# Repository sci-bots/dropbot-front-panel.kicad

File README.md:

# DropBot v3 front panel

The front panel board provides the power (+3.3V, +12V) and communication (i2c) bus for the other boards in the [DropBot v3 system][dropbot] and routes the high-voltage outputs from the switching boards to the pogo-pin board.

For more information, please visit https://sci-bots.com

[][sci-bots]

This design is open-source hardware released under a [Creative Commons Attribution-ShareAlike licence][cc-by-sa].

[][cc-by-sa]

[dropbot]: https://github.com/sci-bots/dropbot-v3
[sci-bots]: https://sci-bots.com/
[cc-by-sa]: http://creativecommons.org/licenses/by-sa/3.0

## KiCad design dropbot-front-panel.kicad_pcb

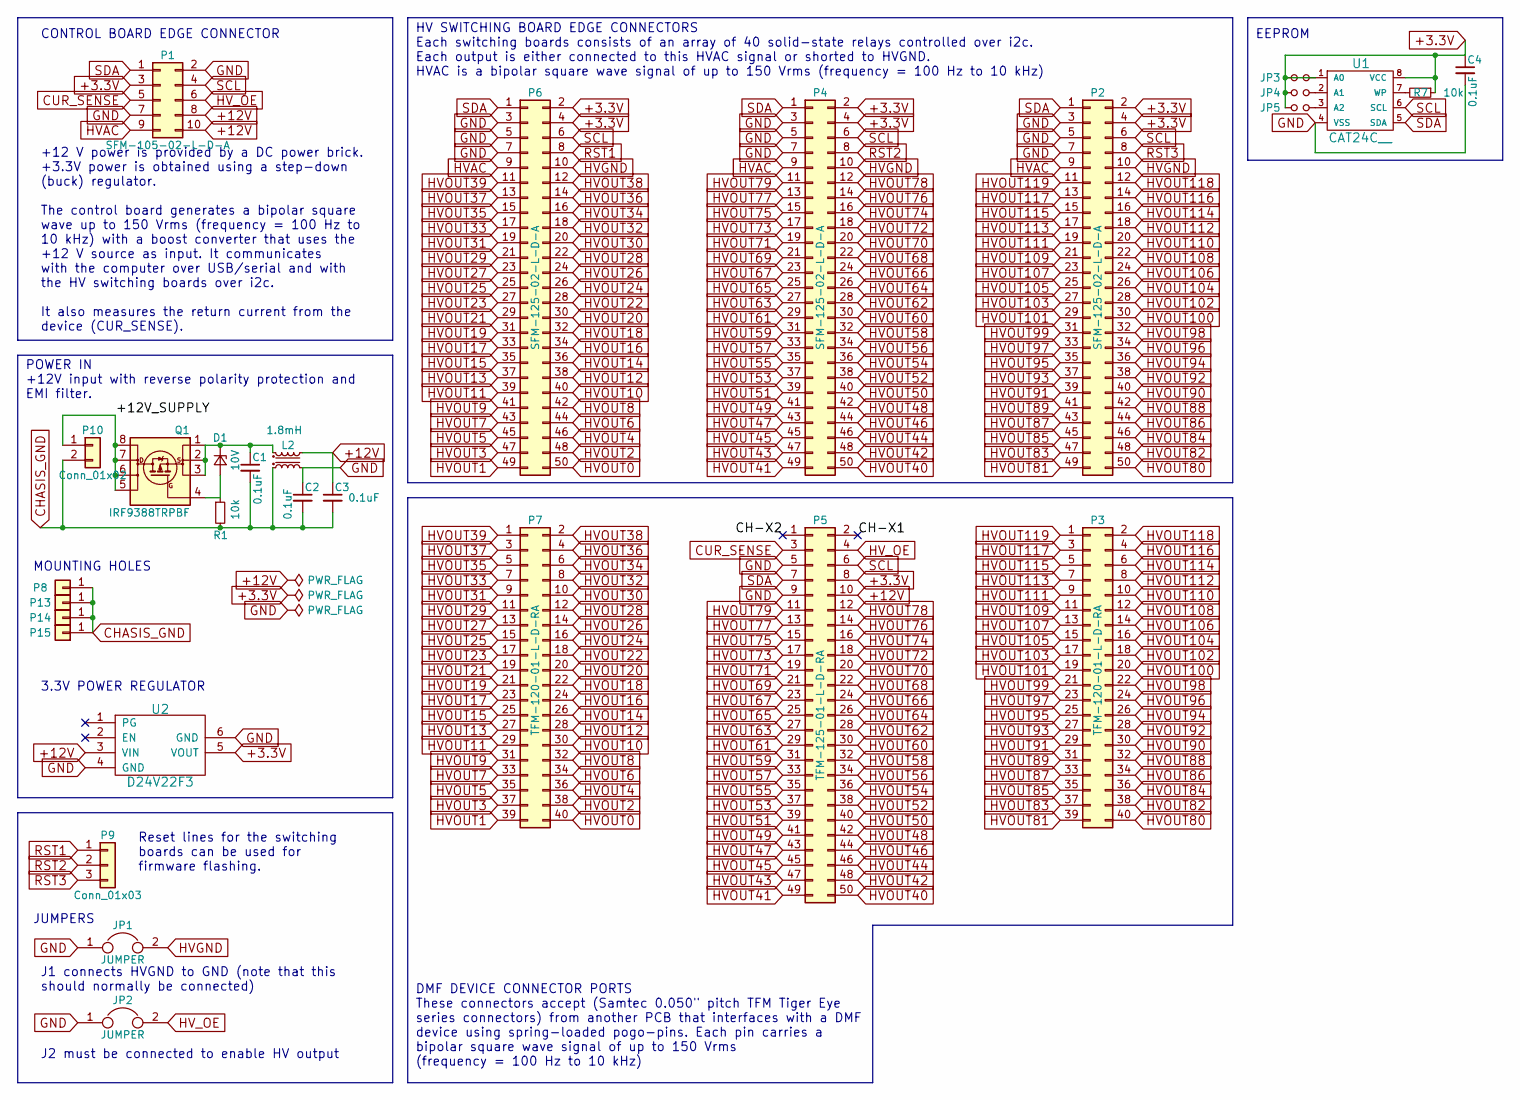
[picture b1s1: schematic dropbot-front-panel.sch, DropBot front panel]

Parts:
C1, C2, C3, C4: 0.1uF; C_0805; MPN CL21B104KBCNNNC
D1: 10V; D_SOD-323; MPN MMSZ5240BS-7-F
JP1: JUMPER; R_0805; MPN RC0805JR-070RL
JP2: JUMPER; R_0805; MPN DNP
JP3: A0; R_0603; MPN DNP
JP4: A1; R_0603; MPN DNP
JP5: A2; R_0603; MPN DNP
L2: 1.8mH; RN242-X-02-XXX; MPN RN242-6-02-1M8
P1: SFM-105-02-L-D-A; SFM-105-02-XXX-D-A; MPN SFM-105-02-L-D-A
P2, P4, P6: SFM-125-02-L-D-A; SFM-125-02-XXX-D-A; MPN TFM-120-01-L-D-RA
P3, P7: TFM-120-01-L-D-RA; TFM-120-01-XXX-D-RA; MPN TFM-125-01-L-D-RA
P5: TFM-125-01-L-D-RA; TFM-125-01-XXX-D-RA; MPN DNP
P8, P13, P14, P15: Conn_01x01; 1pin; MPN SFM-125-02-L-D-A
P9: Conn_01x03; Pin_Header_Straight_1x03; MPN DNP
P10: Conn_01x02; bornier2; MPN DNP
Q1: IRF9388TRPBF; SO-8; MPN IRF9388TRPBF
R1, R7: 10k; R_0805; MPN RC0805FR-0710KL
U1: CAT24C__; TSSOP-8_4.4x3mm_Pitch0.65mm; MPN M24C02-DRDW8TP/K
U2: D24V22F3; D24V22F; MPN D24V22F3

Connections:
+3.3V: C4.1, JP3.1, JP3.2, JP4.1, JP5.1, P1.3, P2.2, P2.4, P4.2, P4.4, P5.8, P6.2, P6.4, R7.1, U1.1 (A0), U1.8 (VCC), U2.5 (VOUT)
+12V: C3.1, L2.2, P1.8, P1.10, P5.10, U2.3 (VIN)
/+12V_SUPPLY: P10.1, Q1.5 (D), Q1.6 (D), Q1.7 (D), Q1.8 (D)
/CH-X1: P5.2
/CH-X2: P5.1
CHASIS_GND: C1.2, C2.2, C3.2, L2.4, P8.1, P10.2, P13.1, P14.1, P15.1, R1.2
CUR_SENSE: P1.5, P5.3
GND: C2.1, C4.2, JP1.1, JP2.1, L2.3, P1.2, P1.7, P2.3, P2.5, P2.7, P4.3, P4.5, P4.7, P5.5, P5.9, P6.3, P6.5, P6.7, U1.4 (VSS), U2.4 (GND), U2.6 (GND)
HVAC: P1.9, P2.9, P4.9, P6.9
HVGND: JP1.2, P2.10, P4.10, P6.10
HVOUT0: P6.50, P7.40
HVOUT1: P6.49, P7.39
HVOUT2: P6.48, P7.38
HVOUT3: P6.47, P7.37
HVOUT4: P6.46, P7.36
HVOUT5: P6.45, P7.35
HVOUT6: P6.44, P7.34
HVOUT7: P6.43, P7.33
HVOUT8: P6.42, P7.32
HVOUT9: P6.41, P7.31
HVOUT10: P6.40, P7.30
HVOUT11: P6.39, P7.29
HVOUT12: P6.38, P7.28
HVOUT13: P6.37, P7.27
HVOUT14: P6.36, P7.26
HVOUT15: P6.35, P7.25
HVOUT16: P6.34, P7.24
HVOUT17: P6.33, P7.23
HVOUT18: P6.32, P7.22
HVOUT19: P6.31, P7.21
HVOUT20: P6.30, P7.20
HVOUT21: P6.29, P7.19
HVOUT22: P6.28, P7.18
HVOUT23: P6.27, P7.17
HVOUT24: P6.26, P7.16
HVOUT25: P6.25, P7.15
HVOUT26: P6.24, P7.14
HVOUT27: P6.23, P7.13
HVOUT28: P6.22, P7.12
HVOUT29: P6.21, P7.11
HVOUT30: P6.20, P7.10
HVOUT31: P6.19, P7.9
HVOUT32: P6.18, P7.8
HVOUT33: P6.17, P7.7
HVOUT34: P6.16, P7.6
HVOUT35: P6.15, P7.5
HVOUT36: P6.14, P7.4
HVOUT37: P6.13, P7.3
HVOUT38: P6.12, P7.2
HVOUT39: P6.11, P7.1
HVOUT40: P4.50, P5.50
HVOUT41: P4.49, P5.49
HVOUT42: P4.48, P5.48
HVOUT43: P4.47, P5.47
HVOUT44: P4.46, P5.46
HVOUT45: P4.45, P5.45
HVOUT46: P4.44, P5.44
HVOUT47: P4.43, P5.43
HVOUT48: P4.42, P5.42
HVOUT49: P4.41, P5.41
HVOUT50: P4.40, P5.40
HVOUT51: P4.39, P5.39
HVOUT52: P4.38, P5.38
HVOUT53: P4.37, P5.37
HVOUT54: P4.36, P5.36
HVOUT55: P4.35, P5.35
HVOUT56: P4.34, P5.34
HVOUT57: P4.33, P5.33
HVOUT58: P4.32, P5.32
HVOUT59: P4.31, P5.31
HVOUT60: P4.30, P5.30
HVOUT61: P4.29, P5.29
HVOUT62: P4.28, P5.28
HVOUT63: P4.27, P5.27
HVOUT64: P4.26, P5.26
HVOUT65: P4.25, P5.25
HVOUT66: P4.24, P5.24
HVOUT67: P4.23, P5.23
HVOUT68: P4.22, P5.22
HVOUT69: P4.21, P5.21
HVOUT70: P4.20, P5.20
HVOUT71: P4.19, P5.19
HVOUT72: P4.18, P5.18
HVOUT73: P4.17, P5.17
HVOUT74: P4.16, P5.16
HVOUT75: P4.15, P5.15
HVOUT76: P4.14, P5.14
HVOUT77: P4.13, P5.13
HVOUT78: P4.12, P5.12
HVOUT79: P4.11, P5.11
HVOUT80: P2.50, P3.40
HVOUT81: P2.49, P3.39
HVOUT82: P2.48, P3.38
HVOUT83: P2.47, P3.37
HVOUT84: P2.46, P3.36
HVOUT85: P2.45, P3.35
HVOUT86: P2.44, P3.34
HVOUT87: P2.43, P3.33
HVOUT88: P2.42, P3.32
HVOUT89: P2.41, P3.31
HVOUT90: P2.40, P3.30
HVOUT91: P2.39, P3.29
HVOUT92: P2.38, P3.28
HVOUT93: P2.37, P3.27
HVOUT94: P2.36, P3.26
HVOUT95: P2.35, P3.25
HVOUT96: P2.34, P3.24
HVOUT97: P2.33, P3.23
HVOUT98: P2.32, P3.22
HVOUT99: P2.31, P3.21
HVOUT100: P2.30, P3.20
HVOUT101: P2.29, P3.19
HVOUT102: P2.28, P3.18
HVOUT103: P2.27, P3.17
HVOUT104: P2.26, P3.16
HVOUT105: P2.25, P3.15
HVOUT106: P2.24, P3.14
HVOUT107: P2.23, P3.13
HVOUT108: P2.22, P3.12
HVOUT109: P2.21, P3.11
HVOUT110: P2.20, P3.10
HVOUT111: P2.19, P3.9
HVOUT112: P2.18, P3.8
HVOUT113: P2.17, P3.7
HVOUT114: P2.16, P3.6
HVOUT115: P2.15, P3.5
HVOUT116: P2.14, P3.4
HVOUT117: P2.13, P3.3
HVOUT118: P2.12, P3.2
HVOUT119: P2.11, P3.1
HV_OE: JP2.2, P1.6, P5.4
unnamed: C1.1, D1.1 (K), L2.1, Q1.1 (S), Q1.2 (S), Q1.3 (S)
unnamed: D1.2 (A), Q1.4 (G), R1.1
unnamed: JP4.2, U1.2 (A1)
unnamed: JP5.2, U1.3 (A2)
unnamed: R7.2, U1.7 (WP)
RST1: P6.8, P9.1
RST2: P4.8, P9.2
RST3: P2.8, P9.3
SCL: P1.4, P2.6, P4.6, P5.6, P6.6, U1.6 (SCL)
SDA: P1.1, P2.1, P4.1, P5.7, P6.1, U1.5 (SDA)

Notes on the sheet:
CONTROL BOARD EDGE CONNECTOR
HV SWITCHING BOARD EDGE CONNECTORS Each switching boards consists of an array of 40 solid-state relays controlled over i2c. Each output is either connected to this HVAC signal or shorted to HVGND. HVAC is a bipolar square wave signal of up to 150 Vrms (frequency = 100 Hz to 10 kHz)
DMF DEVICE CONNECTOR PORTS These connectors accept (Samtec 0.050" pitch TFM Tiger Eye series connectors) from another PCB that interfaces with a DMF device using spring-loaded pogo-pins. Each pin carries a bipolar square wave signal of up to 150 Vrms (frequency = 100 Hz to 10 kHz)
JUMPERS
J1 connects HVGND to GND (note that this should normally be connected)
J2 must be connected to enable HV output
+12 V power is provided by a DC power brick. +3.3V power is obtained using a step-down (buck) regulator. The control board generates a bipolar square wave up to 150 Vrms (frequency = 100 Hz to 10 kHz) with a boost converter that uses the +12 V source as input. It communicates with the computer over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
Reset lines for the switching boards can be used for firmware flashing.
3.3V POWER REGULATOR
POWER IN +12V input with reverse polarity protection and EMI filter.
MOUNTING HOLES
EEPROM

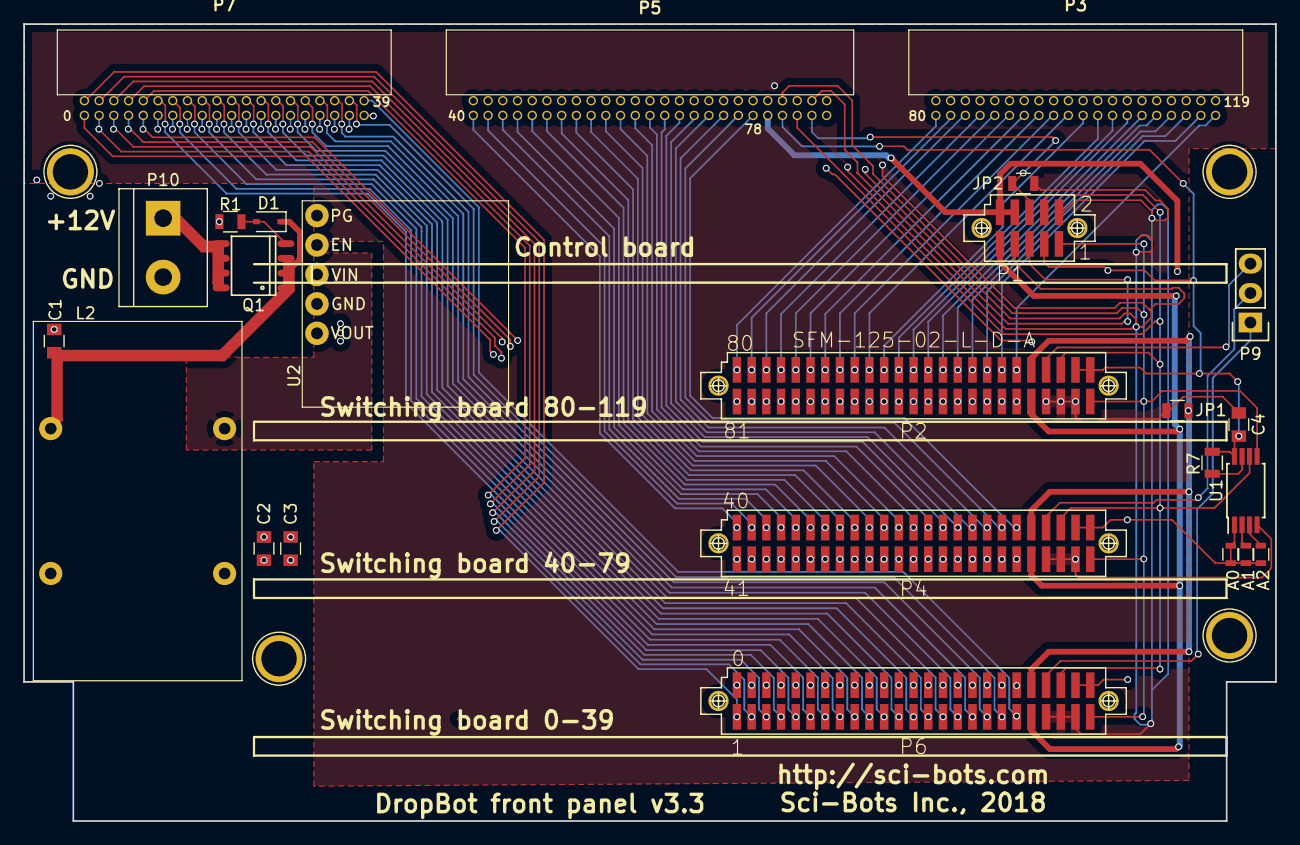
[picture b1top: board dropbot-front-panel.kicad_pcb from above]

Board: 4 copper layers, 108.0 x 68.8 mm, 29 parts (0 on the bottom side), 139 nets.

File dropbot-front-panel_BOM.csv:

Reference,Value,Footprint,Count,Datasheet,Mfg_Part_No
"JP1, JP2",JUMPER,Resistors_SMD:R_0805,2,,RC0805JR-070RL
U2,D24V22F3,Sci-Bots:D24V22F,1,,
Q1,IRF9388TRPBF,Power_Integrations:SO-8,1,,IRF9388TRPBF
L2,1.8mH,Sci-Bots:RN242-X-02-XXX,1,,RN242-6-02-1M8
"C1, C2, C3, C4",0.1uF,Capacitors_SMD:C_0805,4,,CL21B104KBCNNNC
"R1, R7",10k,Resistors_SMD:R_0805,2,,RC0805FR-0710KL
D1,10V,Diodes_SMD:D_SOD-323,1,,MMSZ5240BS-7-F
U1,I2C_EEPROM,Housings_SSOP:TSSOP-8_4.4x3mm_Pitch0.65mm,1,,M24C02-DRDW8TP/K
JP3,A0,Resistors_SMD:R_0603,1,,
JP4,A1,Resistors_SMD:R_0603,1,,
JP5,A2,Resistors_SMD:R_0603,1,,
P10,Conn_01x02,Connect:bornier2,1,,
"P8, P13, P14, P15",Conn_01x01,Connect:1pin,4,,
P9,Conn_01x03,Pin_Headers:Pin_Header_Straight_1x03,1,,
P1,SFM-105-02-L-D-A,Sci-Bots:SFM-105-02-XXX-D-A,1,,SFM-105-02-L-D-A
"P6, P4, P2",SFM-125-02-L-D-A,Sci-Bots:SFM-125-02-XXX-D-A,3,,SFM-125-02-L-D-A
"P7, P3",TFM-120-01-L-D-RA,Sci-Bots:TFM-120-01-XXX-D-RA,2,,TFM-120-01-L-D-RA
P5,TFM-125-01-L-D-RA,Sci-Bots:TFM-125-01-XXX-D-RA,1,,TFM-125-01-L-D-RA

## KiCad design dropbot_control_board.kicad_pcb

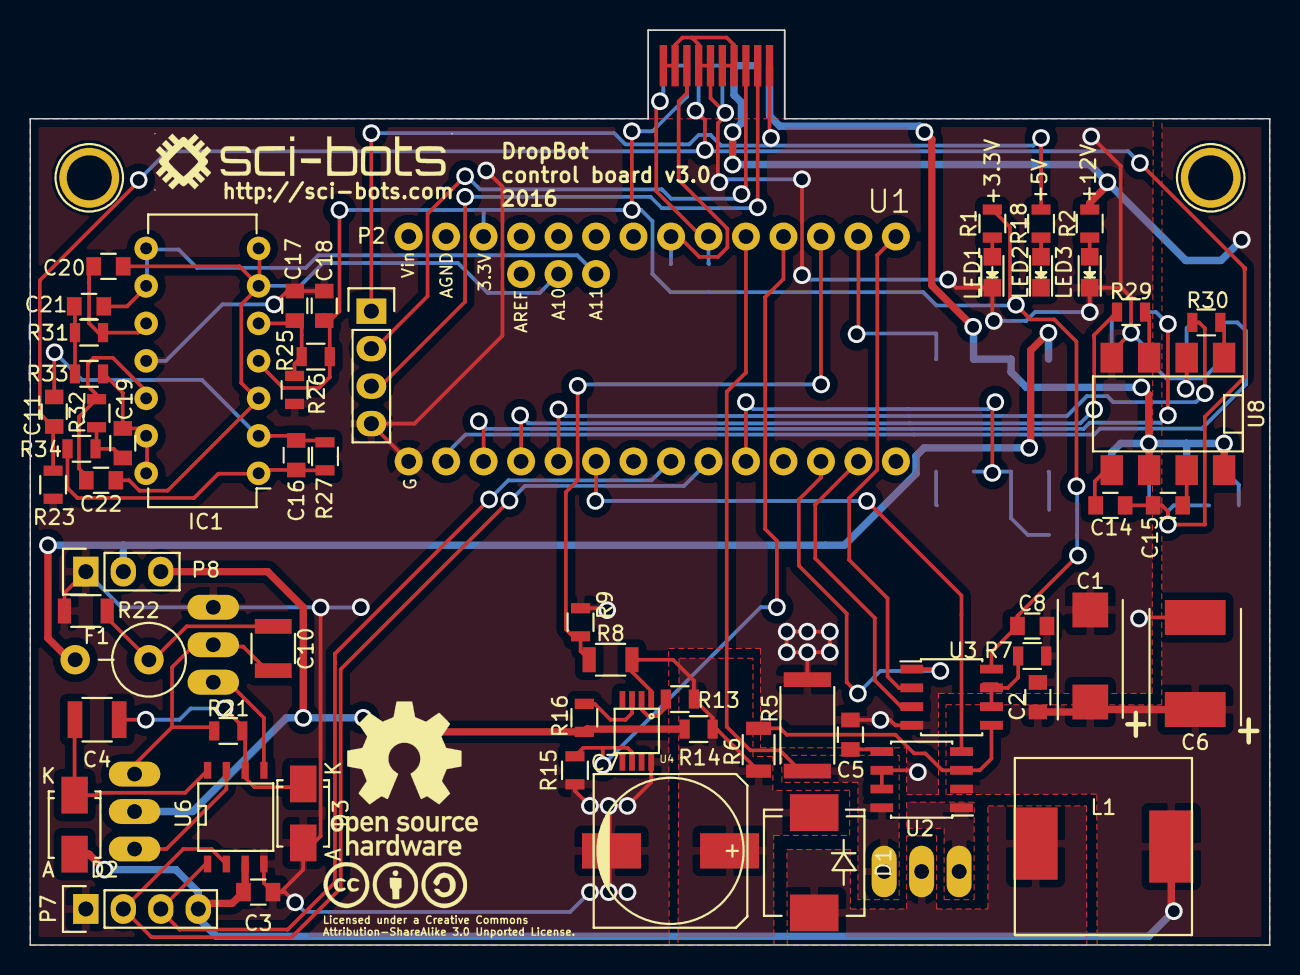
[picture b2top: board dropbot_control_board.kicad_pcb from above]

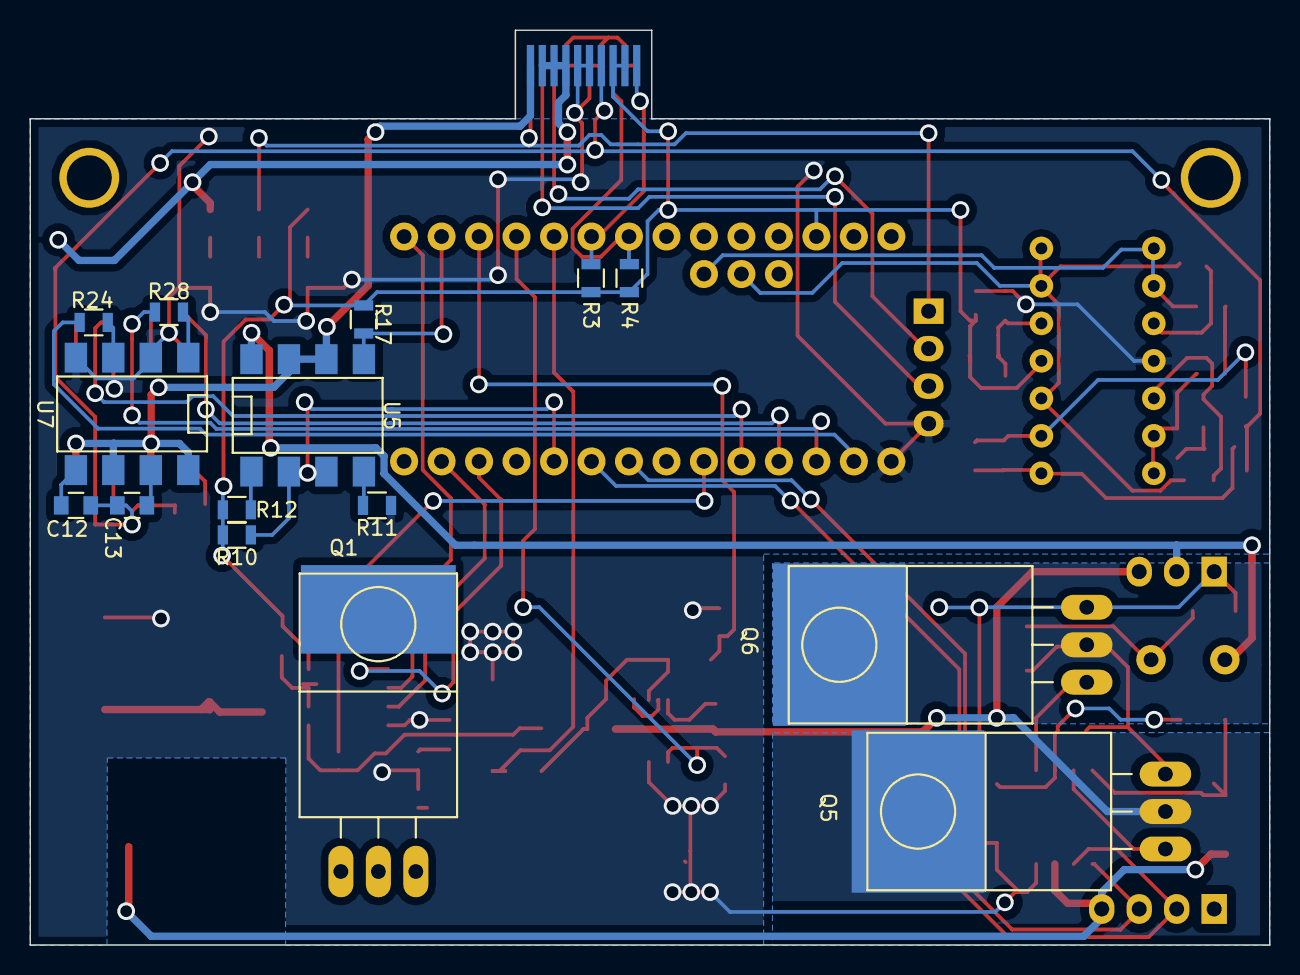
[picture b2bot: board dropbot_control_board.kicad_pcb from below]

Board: 2 copper layers, 84.0 x 62.0 mm, 77 parts (15 on the bottom side), 64 nets.

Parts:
C1: 10uF; TantalC_SizeD_EIA-7343_Reflow
C2, C3, C5, C8, C16, C17, C18: 0.1uF; C_0805
C4, C10: 100n,500V; C_1210
C6: 100uF,35V; TantalC_SizeE_EIA-7360_Reflow
C7: 3.3uF,400V; c_elec_10x10
C11: 1uF; C_0805
C12: 1pF; C_0805
C13: 10pF; C_0805
C14, C20, C22: 100pF; C_0805
C15: 1nF; C_0805
C19: 0.015uF; C_0805
C21: 470pF; C_0805
D1: ES3J; SMC_Standard
D2, D3: D; SMA_Standard
F1: FUSE; Resistor_Vertical_RM5mm
IC1: MCP6024; DIP-14_W7.62mm
L1: 47uH,3.8A; SRR1210
LED1: +3.3V; LED_0805
LED2: +5V; LED_0805
LED3: +12V; LED_0805
P1: CONN_02X10; HSEC8-110-XX-X-RA-MATE
P2, P7: CONN_01X04; Pin_Header_Straight_1x04
P8: CONN_01X03; Pin_Header_Straight_1x03
Q1: STP33N65M2; TO-220_Neutral123_Horizontal_LargePads
Q5, Q6: IRF740BPBF; TO-220_Neutral123_Horizontal_LargePads
R1, R18: 1k; R_0805
R2, R7: 2k; R_0805
R3, R4, R13: 5.1k; R_0805
R5: 30m; R_2512
R6, R8, R22: 2M; R_1206
R9: 20k; R_0805
R10: 4.75k; R_0805
R11, R12, R24, R28, R29, R30: 200; R_0805
R14: 5.1; R_0805
R15, R17: 51k; R_0805
R16: 100k; R_0805
R21: 10; R_0805
R23, R27: 1Meg; R_0805
R25: 10k; R_0805
R26: 2.2k; R_0805
R31: 18.7k; R_0805
R32: 2.1k; R_0805
R33: 14.7k; R_0805
R34: 887; R_0805
U1: Teensy_3.2; Teensy-3.2
U2: MAX1771; SOIC-8_3.9x4.9mm_Pitch1.27mm
U3: MCP41050; SOIC-8_3.9x4.9mm_Pitch1.27mm
U4: HV7802; MSOP-8
U5, U7, U8: DPST (2 Form A), 350V; DIP-8_SMD
U6: NCP5304; SOIC-8-N

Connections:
+0.6V: C20.1, C22.1, IC1.3, IC1.6, IC1.7, U1.34
+3.3V: C8.2, C18.1, IC1.4, P1.3, P1.5, R1.1, R3.1, R4.1, R10.1, R12.2, R17.1, R25.1, U1.24, U3.8
+5V: P1.20, P2.1, R18.1
+12V: C1.1, C2.1, C3.2, C6.1, D2.2, L1.2, P1.13, P1.15, P1.17, P7.4, R2.1, U2.2, U6.3
A0/SHORT_CHK: R17.2, U1.14, U5.5
A1/HV_FB: R8.1, R9.2, U1.15
A2/HV507_CS: R15.2, U1.16, U4.6
A3/MAX1771_CS: Q1.3, R5.1, U1.17, U2.8
A11: C21.1, IC1.8, IC1.9, U1.33
CUR_SENSE: C11.2, C12.2, C13.2, C14.2, C15.2, P1.7, R23.1
D0: R24.1, U1.0
D1: R28.1, U1.1
D2: R29.1, U1.2
D3: R30.1, U1.3
D4/SHDN: U1.4, U2.4
D6/DRIVER_LO: P7.3, U1.6, U6.1
D7/DRIVER_HI: P7.2, U1.7, U6.2
D8/OUTPUT_SELECT: R10.2, U1.8, U5.2, U5.3
D10/MCP41050_CS: U1.10, U3.1
D11/MOSI: U1.11, U3.3
D13/SCK: U1.13, U3.2
D+: P1.18, P2.3
D-: P1.16, P2.2
GND: C1.2, C2.2, C3.1, C5.2, C6.2, C7.2, C8.1, C17.2, C18.2, D3.2, IC1.11, LED1.1, LED3.1, P1.2, P1.4, P1.8, P1.9, P1.10, P1.11, P1.12, P1.14, P2.4, P7.1, P8.1, Q6.3, R5.2, R7.2, R9.1, R11.1, R15.1, R22.2, R23.2, R26.2, U1.27, U2.6, U2.7, U3.4, U4.8, U6.4, U7.2, U7.4, U8.2, U8.4
HV: P8.3, Q5.2, R14.1, R16.2
HVAC: F1.2, P8.2, U5.8
unnamed: C4.1, D3.1, R21.2, U6.6
unnamed: C4.2, D2.1, U6.8
unnamed: C5.1, U2.5
unnamed: C7.1, D1.1, R6.1, R8.2, R13.1, R14.2, U4.1
unnamed: C10.1, Q5.3, Q6.2, R21.1
unnamed: C10.2, F1.1, R22.1
unnamed: C11.1, C16.2, IC1.2, R27.2
unnamed: C12.1, U7.5
unnamed: C13.1, U7.7
unnamed: C14.1, U8.5
unnamed: C15.1, U8.7
unnamed: C16.1, IC1.1, R27.1, R34.1
unnamed: C17.1, IC1.5, R25.2, R26.1
unnamed: C19.1, IC1.13, IC1.14, R33.1
unnamed: C19.2, R32.1, R34.2
unnamed: C20.2, IC1.10, R31.2
unnamed: C21.2, R31.1, R33.2
unnamed: C22.2, IC1.12, R32.2
unnamed: D1.2, L1.1, Q1.2
unnamed: LED1.2, R1.2
unnamed: LED2.2, R18.2
unnamed: LED3.2, R2.2
unnamed: Q1.1, U2.1
unnamed: Q5.1, U6.7
unnamed: Q6.1, U6.5
unnamed: R6.2, U2.3, U3.5
unnamed: R7.1, U3.6, U3.7
unnamed: R11.2, U5.4
unnamed: R12.1, U5.1
unnamed: R13.2, U4.2
unnamed: R16.1, U4.3
unnamed: R24.2, U7.3
unnamed: R28.2, U7.1
unnamed: R29.2, U8.3
unnamed: R30.2, U8.1
SCL: P1.6, R4.2, U1.19
SDA: P1.1, R3.2, U1.18
VOUT: P1.19, U5.6, U5.7, U7.6, U7.8, U8.6, U8.8

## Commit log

2016-12-19 Update documentation on schematic and add pdf output
2016-12-19 Remove control board pcb layout from repo
2017-01-05 Update BOM
2017-01-09 Fix BOM
2017-03-01 Update library (add Samtec parts)
2017-03-01 [WIP] Update PCB to use Samtec connectors
    Update PCB to use Samtec connectors instead of PCB edge connections.
    This is because the edge connector slots are not rated for high-voltage
    (i.e., they are not rated for over 30V).
2017-03-01 Add PCB cut-aways for box stand-offs
2017-03-01 Increase height of PCB to match dims of box
2017-03-02 [WIP] Update to use new Samtec connectors...
    * add USB passthrough
    * add 3.3V power regulator
    * add reverse polarity protection on +12V power line
2017-03-03 [WIP] update USB parts, replace jumpers with 0805 pads
2017-03-05 Add switching/control board outlines
2017-03-07 [WIP] Add EMI suppression, ESD protection
2017-03-08 [WIP] route HV outputs
2017-03-08 [WIP] swap order of switching boards
2017-03-08 [WIP] route power, ground planes
2017-03-09 Finish routing all nets, move components to front of board
2017-03-09 Fix control board connector to match v3.1
2017-03-22 Remove usb passthrough, fix SMT connector...
    * remove usb passthrough
    * fix SMT connector footprints (missing holes)
    * remove USB passthrough (now on control board)
    * move power connector to top of board
    * increase height of cutouts in bottom corners
2017-04-20 Fix part numbers for P3 and P7
2017-04-25 label +12V and G on power connector
2017-04-28 Fix spelling mistake (pannel -> panel)
2017-09-19 Fix #1, #2 and #3
    1. Add i2c EEPROM chip to store serial number, hardware version, etc.
    2. Move C2 and C3 (they currently collide with the 2nd switching board)
    3. Fix reverse polarity protection
2017-09-19 Remove extraneous gerber files
2018-03-09 Update to use Sci-Bots library
2018-03-15 Use through-hole connectors to pogo-pin board
2018-06-08 Update routing of TFM connectors, replace eeprom part
    Fixes #4
2018-07-12 Add README, LICENSE and graphics
2021-11-08 Add kicad-helpers files
2021-11-08 Reorganize folder
2021-11-09 Update to kicad 5
2021-11-09 Add manufacturing folder
2021-11-12 Add tests
2021-11-17 Update submodule
2021-11-18 Use recursive checkout for github action
2021-11-25 Add badges to README
2021-11-25 Update netlist
2021-11-25 Update kicad_helpers files
2021-11-25 Fix ERC errors
2021-11-25 Add filters for DRC
2021-12-02 Update line endings

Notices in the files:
dropbot_control_board.kicad_pcb:
Licensed under a Creative Commons
Attribution-ShareAlike 3.0 Unported License.
